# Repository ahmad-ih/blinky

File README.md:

View this project on [CADLAB.io](https://cadlab.io/project/22769). 

# blinky

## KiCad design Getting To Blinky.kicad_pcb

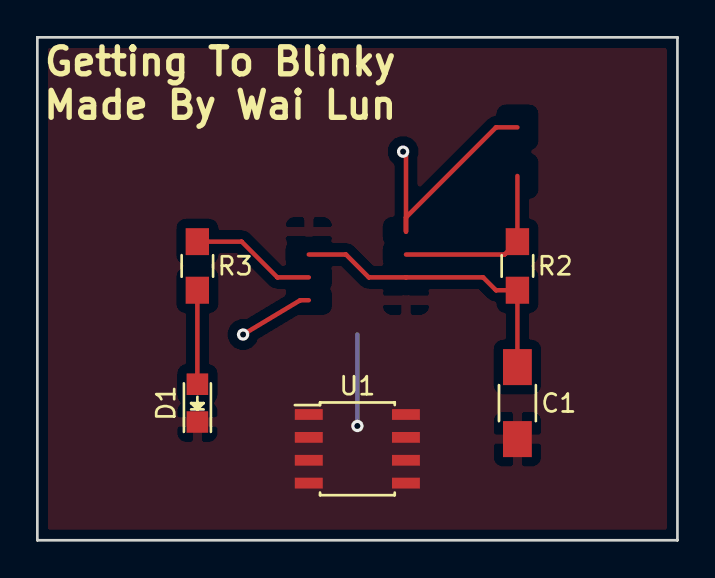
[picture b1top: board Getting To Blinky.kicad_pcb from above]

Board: 2 copper layers, 35.6 x 27.9 mm, 5 parts (0 on the bottom side), 6 nets.

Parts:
C1: 1uF; C_1206_HandSoldering
D1: LED; LED-0805
R2: 470K; R_0805_HandSoldering
R3: 1K; R_0805_HandSoldering
U1: 7555; SOIC-8_3.9x4.9mm_Pitch1.27mm

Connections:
/VDD: U1.4, U1.8
GND: C1.2, D1.1, U1.1, U1.5
unnamed: C1.1, R2.2, U1.2, U1.6
unnamed: D1.2, R3.2
unnamed: R2.1, U1.7
unnamed: R3.1, U1.3

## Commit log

2019-12-20 Added KiCAD files
2019-12-20 Removed R1 from PCB & Battery from Schematic
2019-12-20 Connnected the LED in the Schematic properly
2019-12-20 Displaced 555 IC & Removed Battery Holder Pads
2020-03-26 com 1 gb
2020-03-28 three
2020-03-28 four
2020-03-28 five
2020-03-30 branch tree 1
2020-03-30 branch tree 2
2020-03-30 branch tree 3
2020-03-30 branch tree 4
2020-04-09 Backlink to CADLAB.io has been added.
